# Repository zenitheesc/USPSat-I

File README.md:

<h1 align="center" style="color:white; background-color:black">USP Sat-I</h1>
<h4 align="center">This is an Open Hardware and Software cubesat developed by Zenith EESC-USP for the Cubedesign 2019.</h4>

<p align="center">

</p>

This project was based on a distributed processing architecture and it uses microcontrollers with ARM architecture. The Embedded System is composed by six subsystems:

<a href="https://github.com/zenitheesc/USPSat-AE1/tree/master/M%C3%B3dulo_Ribatski%20v.1.0"><h2>1. Thermal management</h2></a>

This subsystem is primarily responsible for
the active thermal control of the batteries, as proposed by the competition,
in addition to supporting the deployment system of the nanosatellite antennas.

<a href="https://github.com/zenitheesc/USPSat-AE1/tree/master/Varela-Logical_EPS%20v.1.0"><h2>2. Logical EPS</h2></a>

Ensures the monitoring and control of EPS panel parameters,
that is, it performs the measurement of voltage and current levels at various points on the CubeSat;
monitors the temperature of the batteries and acts to keep it always positive, in addition to
carrying out the communication to other subsystems.

<a href="https://github.com/zenitheesc/USPSat-AE1/tree/master/London-Power_EPS%20v.1.1"><h2>3. Power EPS</h2></a>

Functioning as an extension of the previous subsystem, it performs conversions of battery voltage levels to the levels requested within the
hardware, making the necessary distribution, as well as controlling the loading of batteries through solar panels.

<a href="https://github.com/zenitheesc/USPSat-AE1/tree/master/Caurin_CDH%20v.1.0"><h2>4. Comanding and Data Handling</h2></a>

It concentrates one of the processing within CubeSat. It is responsible for managing the information
present in the prototype's internal network, by managing the information received and sent to the Control Base and control of the deployment of the antennas.

<a href="https://github.com/zenitheesc/USPSat-AE1/tree/master/Comin_CTR%20v.1.0"><h2>5. Computer Vision</h2></a>

This subsystem is responsible for image aquisition and on board image processing, for attitude determination using computer vision.

<a href="https://github.com/zenitheesc/USPSat-AE1/tree/master/Alves_ADC%20v.1.0"><h2> 6. Attitude Control </h2></a>

The entire stabilization and pointing system must be done necessary to fulfill the competition missions. For this, the reading is done necessary sensors, activating a reaction wheel, which, by means of the Law of
Conservation of Angular Momentum, manages to act in the attitude of the satellite.

## 7. Structures

Finally, we have the subsystem responsible for the physical integration of all
the subsystems described earlier. All manufacturing issues involving
the physical structure of USPSat is the responsibility of the structures subsystem. The
determination of the materials used, the choice of manufacturing processes and display of all components, aiming at a satisfactory performance in the
vibration, are the main focuses of this subsystem

## Official Documentation

Check out the official documentation [here](https://github.com/zenitheesc/USPSat-AE1/blob/master/USPSat_Report.pdf).

<p align="center">

</p>
<p align = "center">
<a href="zenith.eesc@gmail.com">zenith.eesc@gmail.com</a>
</p>

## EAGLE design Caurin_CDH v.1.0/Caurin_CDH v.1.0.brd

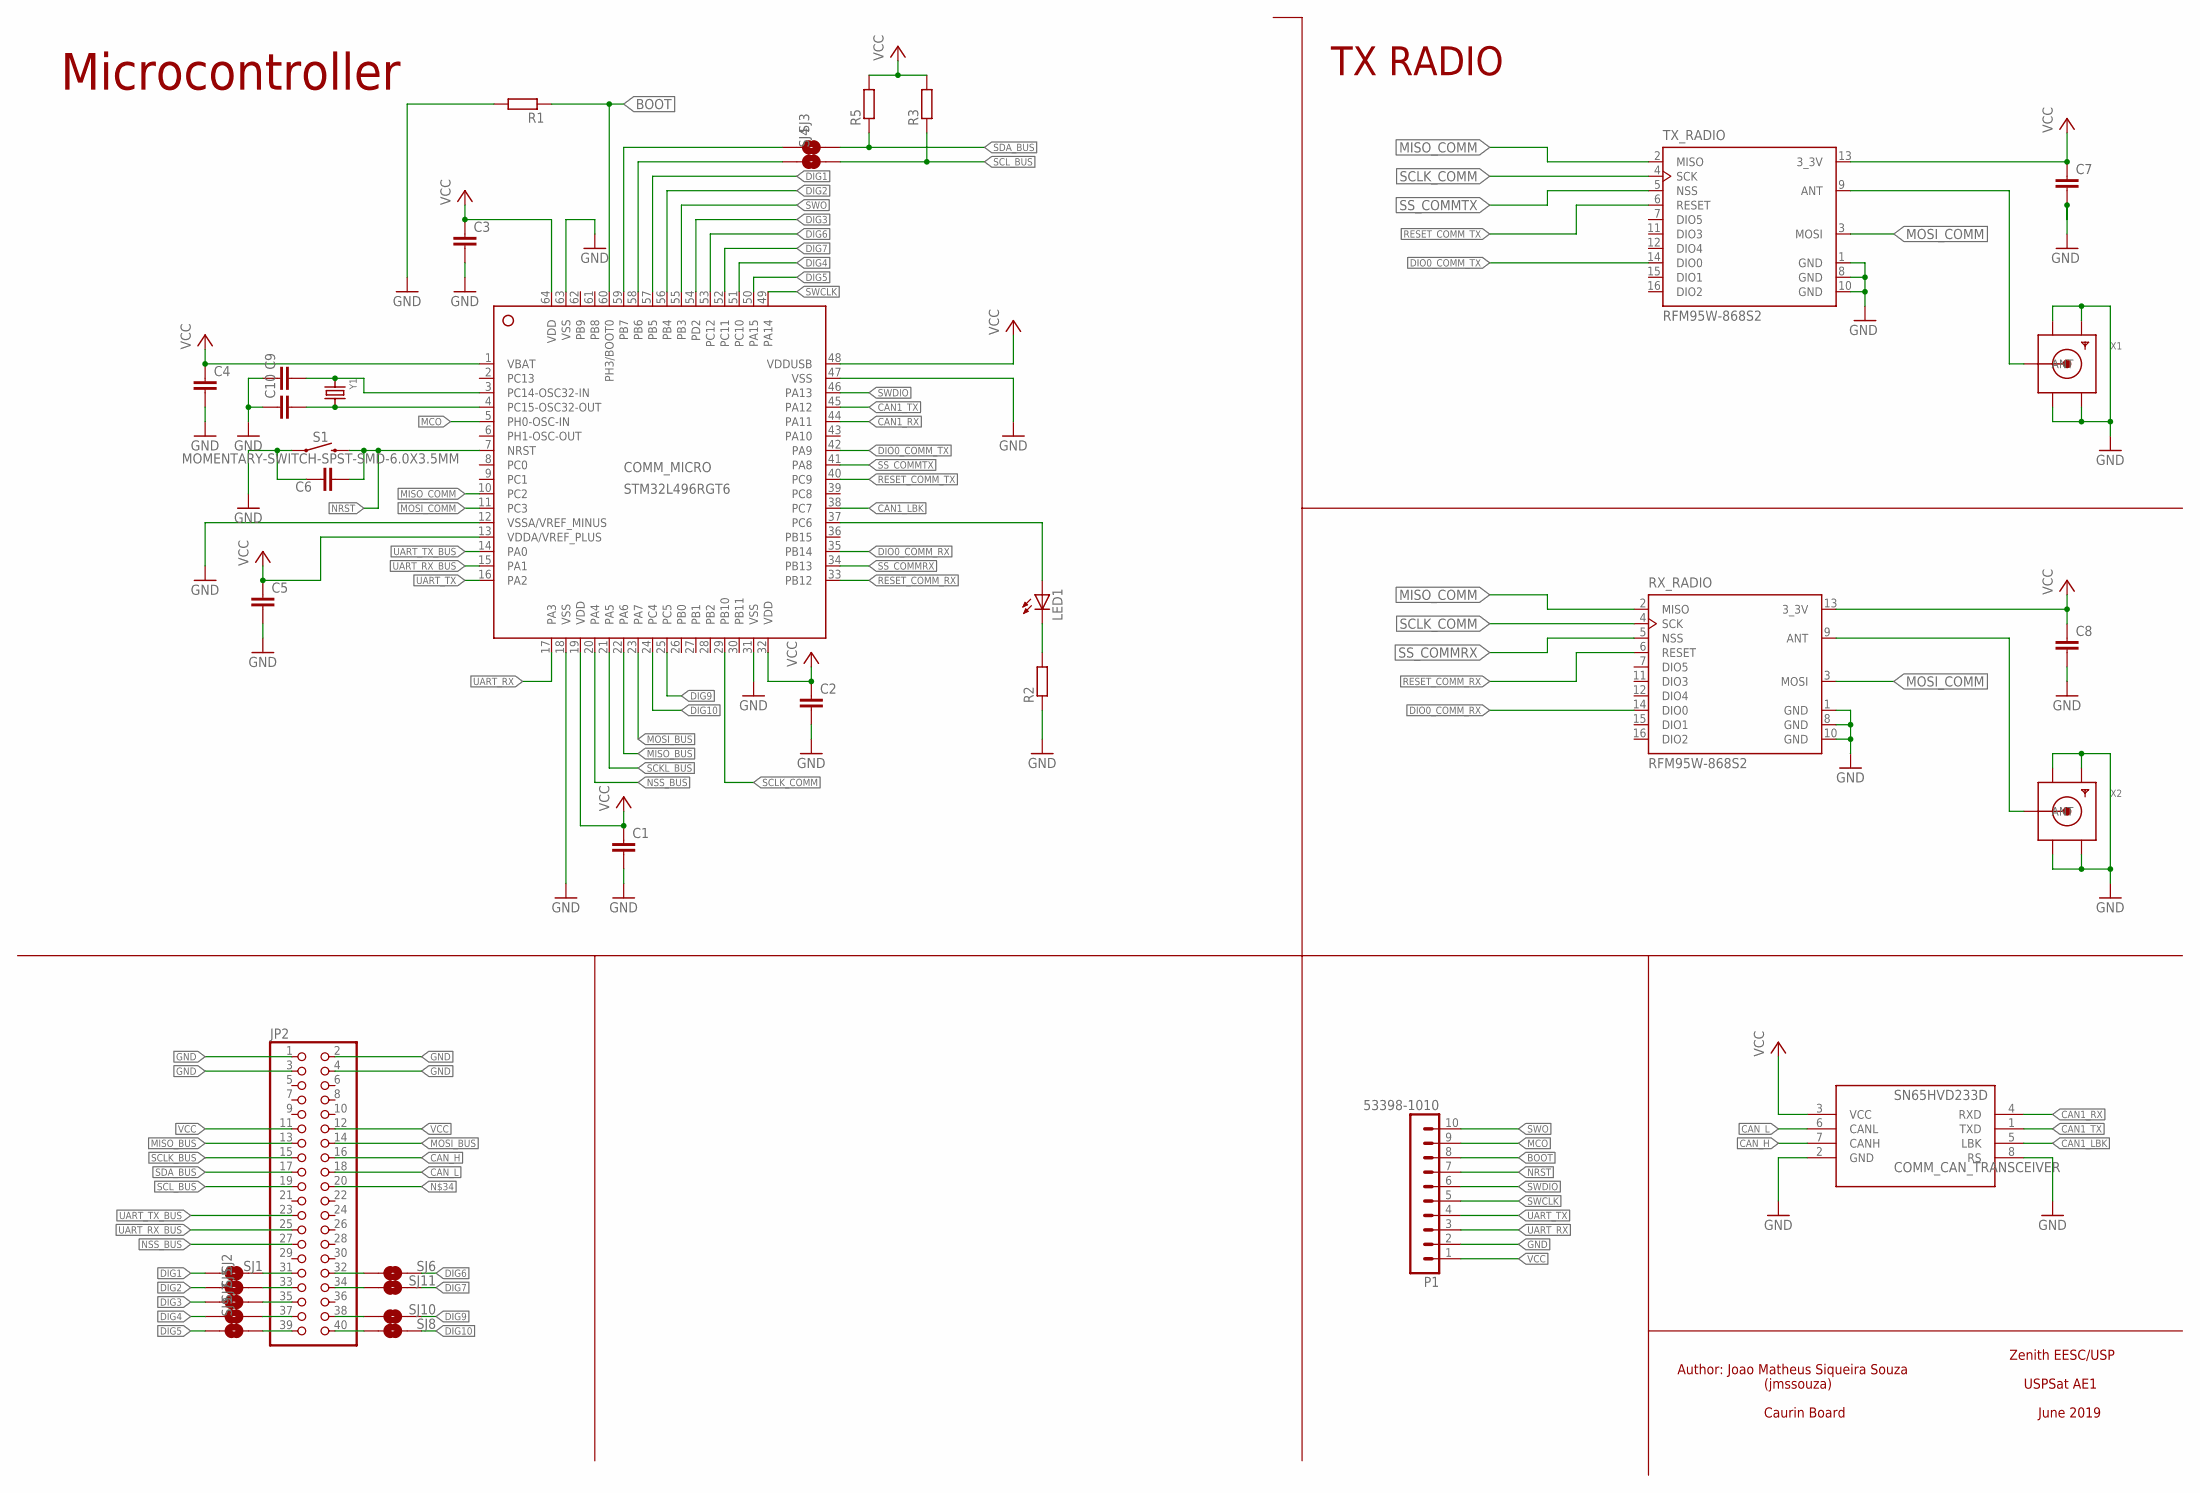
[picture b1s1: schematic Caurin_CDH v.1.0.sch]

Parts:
C1, C2, C3, C4, C5, C6, C7, C8, C9, C10: CC1206; C1206
COMM_CAN_TRANSCEIVER: SN65HVD233D; SOIC8
COMM_MICRO: STM32L496RGT6; LQFP64_10X10
JP2: PINHD-2X20; 2X20
LED1: LED_E; LED_1206
P1: 53398-1010
R1, R2, R3, R5: RR1206; R1206
RX_RADIO: RFM95W-868S2; XCVR_RFM95W-868S2
S1: MOMENTARY-SWITCH-SPST-SMD-6.0X3.5MM; TACTILE_SWITCH_SMD_6.0X3.5MM
SJ1, SJ2, SJ3, SJ4, SJ5, SJ6, SJ7, SJ8, SJ9, SJ10, SJ11: SMD-JUMPER-2
TX_RADIO: RFM95W-868S2; XCVR_RFM95W-868S2
X1, X2: SMACONNECTOR; SMA90_DIP
Y1: CRYSTAL8X3.8SMT; CRYSTAL_8X3.8

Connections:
BOOT: COMM_MICRO.60 (PH3/BOOT0), P1.8, R1.1
CAN1_LBK: COMM_CAN_TRANSCEIVER.5 (LBK), COMM_MICRO.38 (PC7)
CAN1_RX: COMM_CAN_TRANSCEIVER.4 (RXD), COMM_MICRO.44 (PA11)
CAN1_TX: COMM_CAN_TRANSCEIVER.1 (TXD), COMM_MICRO.45 (PA12)
CAN_H: COMM_CAN_TRANSCEIVER.7 (CANH), JP2.16
CAN_L: COMM_CAN_TRANSCEIVER.6 (CANL), JP2.18
DIG1: COMM_MICRO.57 (PB5), SJ1.1
DIG2: COMM_MICRO.56 (PB4), SJ2.1
DIG3: COMM_MICRO.54 (PD2), SJ5.1
DIG4: COMM_MICRO.51 (PC10), SJ7.1
DIG5: COMM_MICRO.50 (PA15), SJ9.1
DIG6: COMM_MICRO.53 (PC12), SJ6.2
DIG7: COMM_MICRO.52 (PC11), SJ11.2
DIG9: COMM_MICRO.25 (PC5), SJ10.2
DIG10: COMM_MICRO.24 (PC4), SJ8.2
DIO0_COMM_RX: COMM_MICRO.35 (PB14), RX_RADIO.14 (DIO0)
DIO0_COMM_TX: COMM_MICRO.42 (PA9), TX_RADIO.14 (DIO0)
GND: C1.2, C2.2, C3.2, C4.2, C5.2, C6.1, C7.2, C8.2, C9.1, C10.1, COMM_CAN_TRANSCEIVER.2 (GND), COMM_CAN_TRANSCEIVER.8 (RS), COMM_MICRO.12 (VSSA/VREF_MINUS), COMM_MICRO.18 (VSS), COMM_MICRO.31 (VSS), COMM_MICRO.47 (VSS), COMM_MICRO.63 (VSS), JP2.1, JP2.2, JP2.3, JP2.4, P1.2, R1.2, R2.1, RX_RADIO.1 (GND), RX_RADIO.8 (GND), RX_RADIO.10 (GND), S1.1, TX_RADIO.1 (GND), TX_RADIO.8 (GND), TX_RADIO.10 (GND), X1.GND1, X1.GND2, X1.GND3, X1.GND4, X2.GND1, X2.GND2, X2.GND3, X2.GND4
MCO: COMM_MICRO.5 (PH0-OSC-IN), P1.9
MISO_BUS: COMM_MICRO.22 (PA6), JP2.13
MISO_COMM: COMM_MICRO.10 (PC2), RX_RADIO.2 (MISO), TX_RADIO.2 (MISO)
MOSI_BUS: COMM_MICRO.23 (PA7), JP2.14
MOSI_COMM: COMM_MICRO.11 (PC3), RX_RADIO.3 (MOSI), TX_RADIO.3 (MOSI)
unnamed: RX_RADIO.9 (ANT), X2.ANTENNA (ANT)
unnamed: COMM_MICRO.37 (PC6), LED1.A
unnamed: LED1.C, R2.2
unnamed: C9.2, COMM_MICRO.3 (PC14-OSC32-IN), Y1.P$1 (1)
unnamed: C10.2, COMM_MICRO.4 (PC15-OSC32-OUT), Y1.P$4 (2)
unnamed: TX_RADIO.9 (ANT), X1.ANTENNA (ANT)
unnamed: JP2.32, SJ6.1
unnamed: COMM_MICRO.59 (PB7), SJ3.1
unnamed: COMM_MICRO.58 (PB6), SJ4.1
unnamed: JP2.34, SJ11.1
unnamed: JP2.38, SJ10.1
unnamed: JP2.40, SJ8.1
unnamed: JP2.37, SJ7.2
unnamed: JP2.39, SJ9.2
unnamed: JP2.35, SJ5.2
unnamed: JP2.33, SJ2.2
unnamed: JP2.31, SJ1.2
NRST: C6.2, COMM_MICRO.7 (NRST), P1.7, S1.2
NSS_BUS: COMM_MICRO.20 (PA4), JP2.27
RESET_COMM_RX: COMM_MICRO.33 (PB12), RX_RADIO.6 (RESET)
RESET_COMM_TX: COMM_MICRO.40 (PC9), TX_RADIO.6 (RESET)
SCKL_BUS: COMM_MICRO.21 (PA5)
SCLK_BUS: JP2.15
SCLK_COMM: COMM_MICRO.29 (PB10), RX_RADIO.4 (SCK), TX_RADIO.4 (SCK)
SCL_BUS: JP2.19, R3.1, SJ4.2
SDA_BUS: JP2.17, R5.1, SJ3.2
SS_COMMRX: COMM_MICRO.34 (PB13), RX_RADIO.5 (NSS)
SS_COMMTX: COMM_MICRO.41 (PA8), TX_RADIO.5 (NSS)
SWCLK: COMM_MICRO.49 (PA14), P1.5
SWDIO: COMM_MICRO.46 (PA13), P1.6
SWO: COMM_MICRO.55 (PB3), P1.10
UART_RX: COMM_MICRO.17 (PA3), P1.3
UART_RX_BUS: COMM_MICRO.15 (PA1), JP2.25
UART_TX: COMM_MICRO.16 (PA2), P1.4
UART_TX_BUS: COMM_MICRO.14 (PA0), JP2.23
VCC: C1.1, C2.1, C3.1, C4.1, C5.1, C7.1, C8.1, COMM_CAN_TRANSCEIVER.3 (VCC), COMM_MICRO.1 (VBAT), COMM_MICRO.13 (VDDA/VREF_PLUS), COMM_MICRO.19 (VDD), COMM_MICRO.32 (VDD), COMM_MICRO.48 (VDDUSB), COMM_MICRO.64 (VDD), JP2.11, JP2.12, P1.1, R3.2, R5.2, RX_RADIO.13 (3_3V), TX_RADIO.13 (3_3V)

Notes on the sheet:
TX RADIO
Author: Joao Matheus Siqueira Souza
Zenith EESC/USP
USPSat AE1
(jmssouza)
June 2019
Caurin Board
Microcontroller

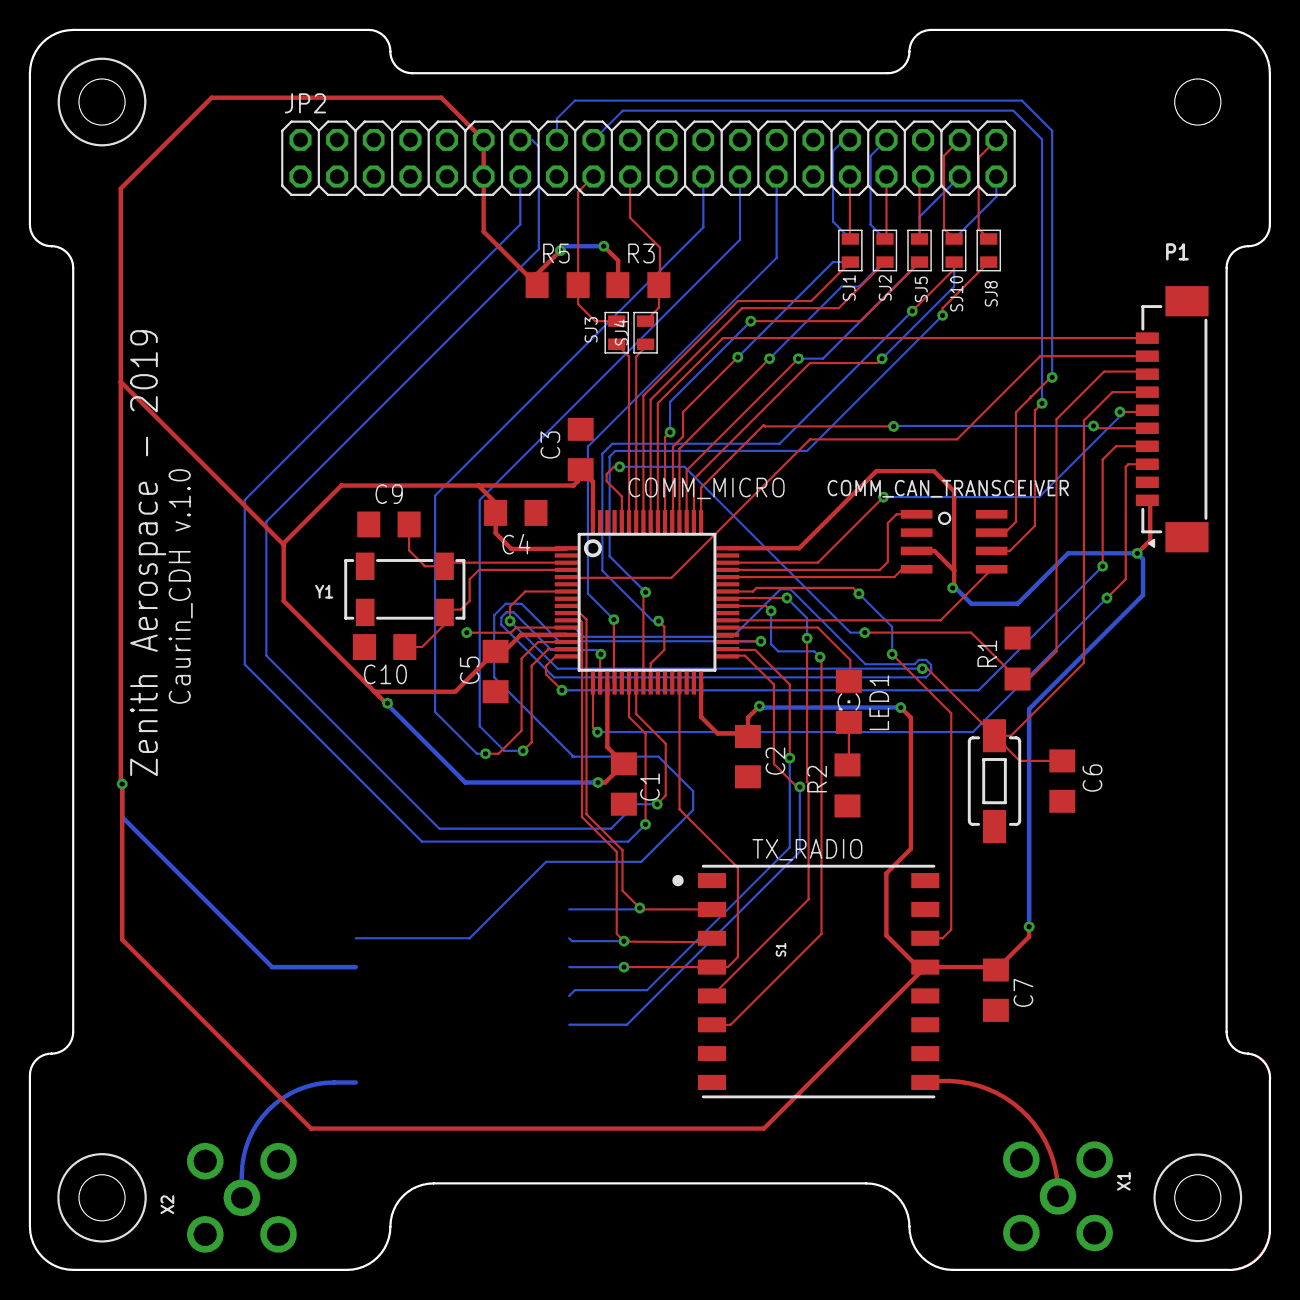
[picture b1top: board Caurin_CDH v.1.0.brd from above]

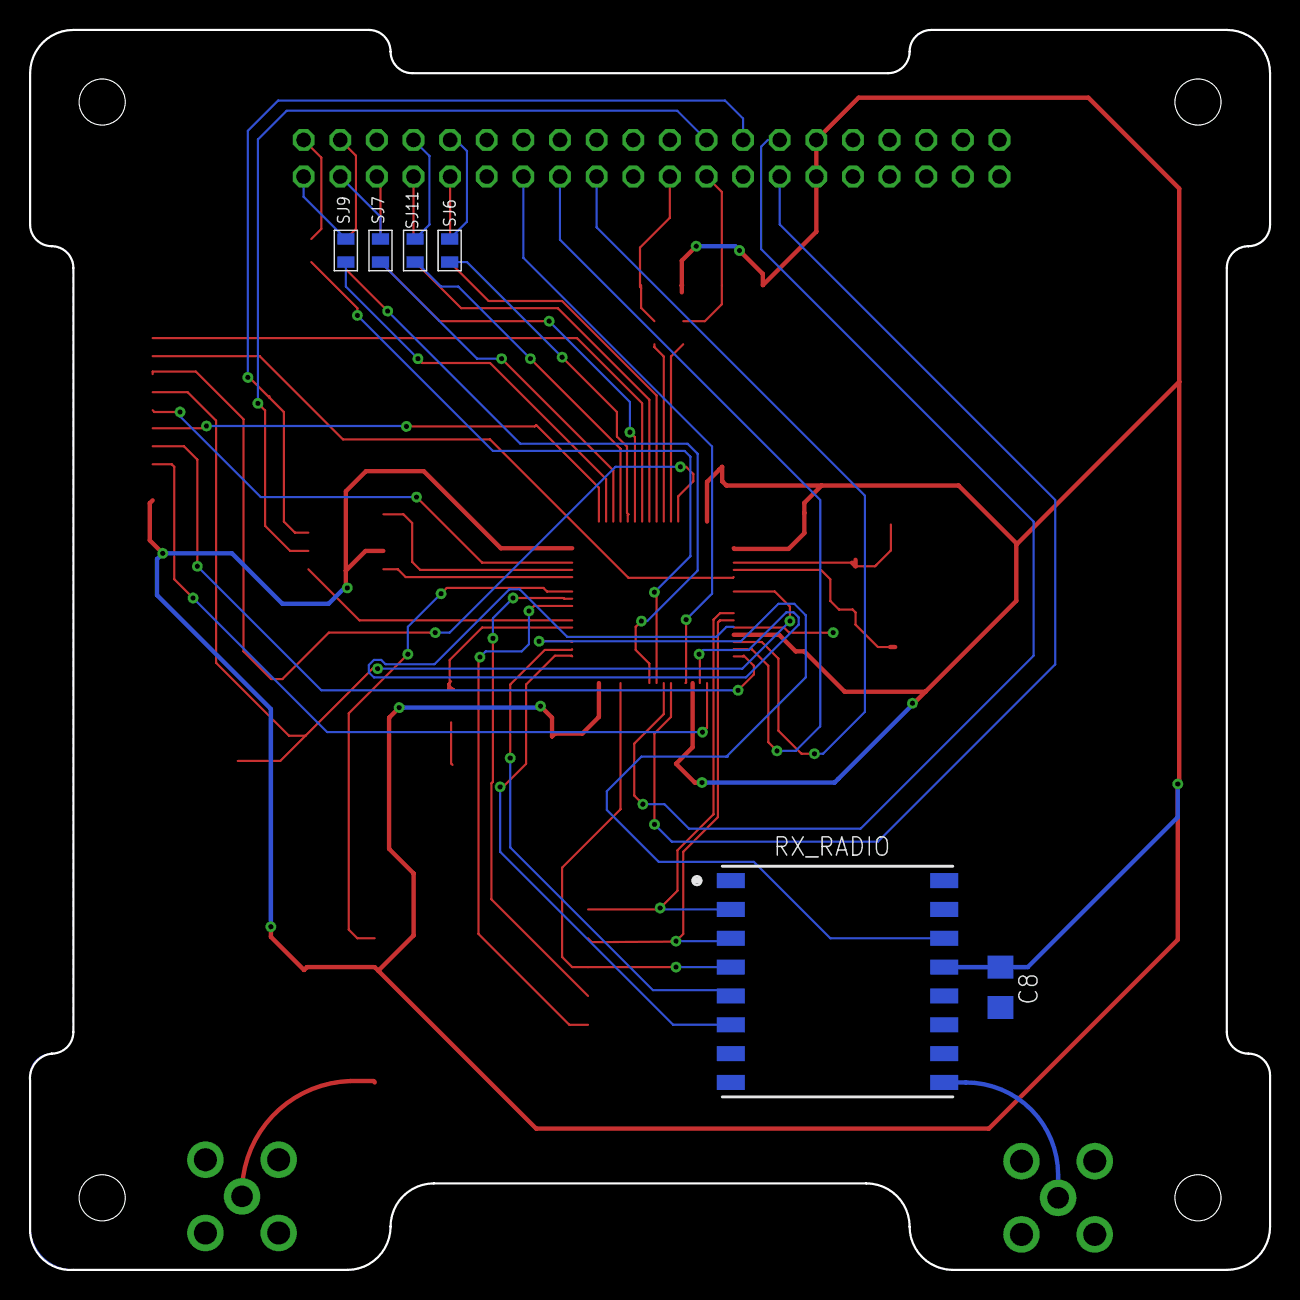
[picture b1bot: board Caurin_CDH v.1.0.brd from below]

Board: 2 copper layers, 86.0 x 86.0 mm, 36 parts (6 on the bottom side), 57 nets.

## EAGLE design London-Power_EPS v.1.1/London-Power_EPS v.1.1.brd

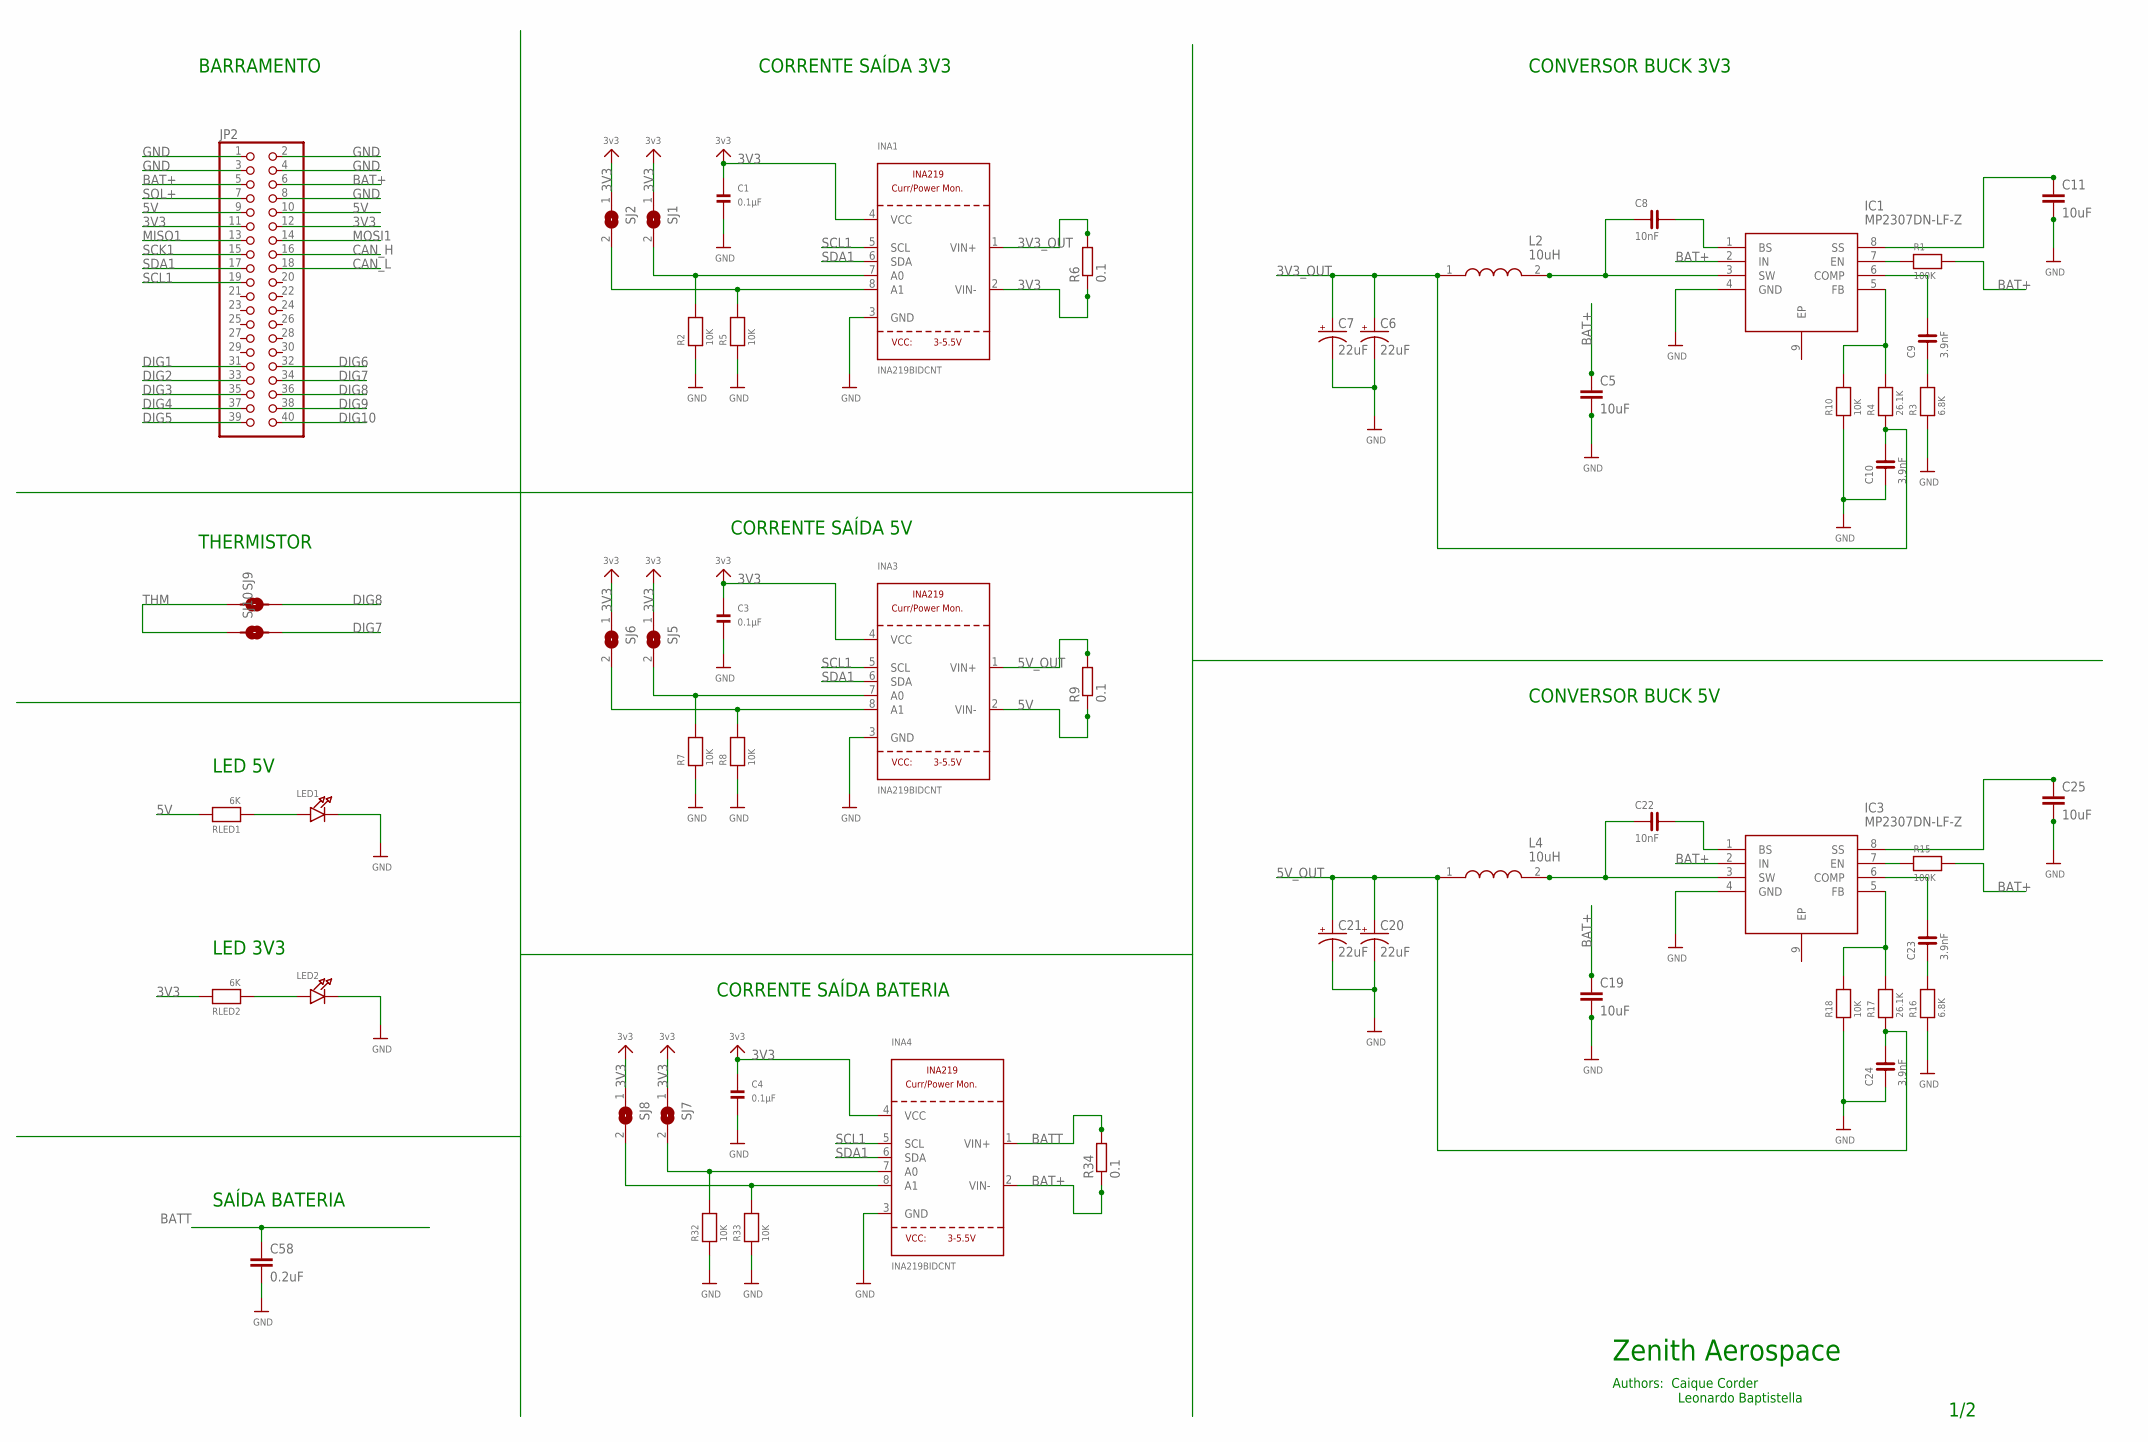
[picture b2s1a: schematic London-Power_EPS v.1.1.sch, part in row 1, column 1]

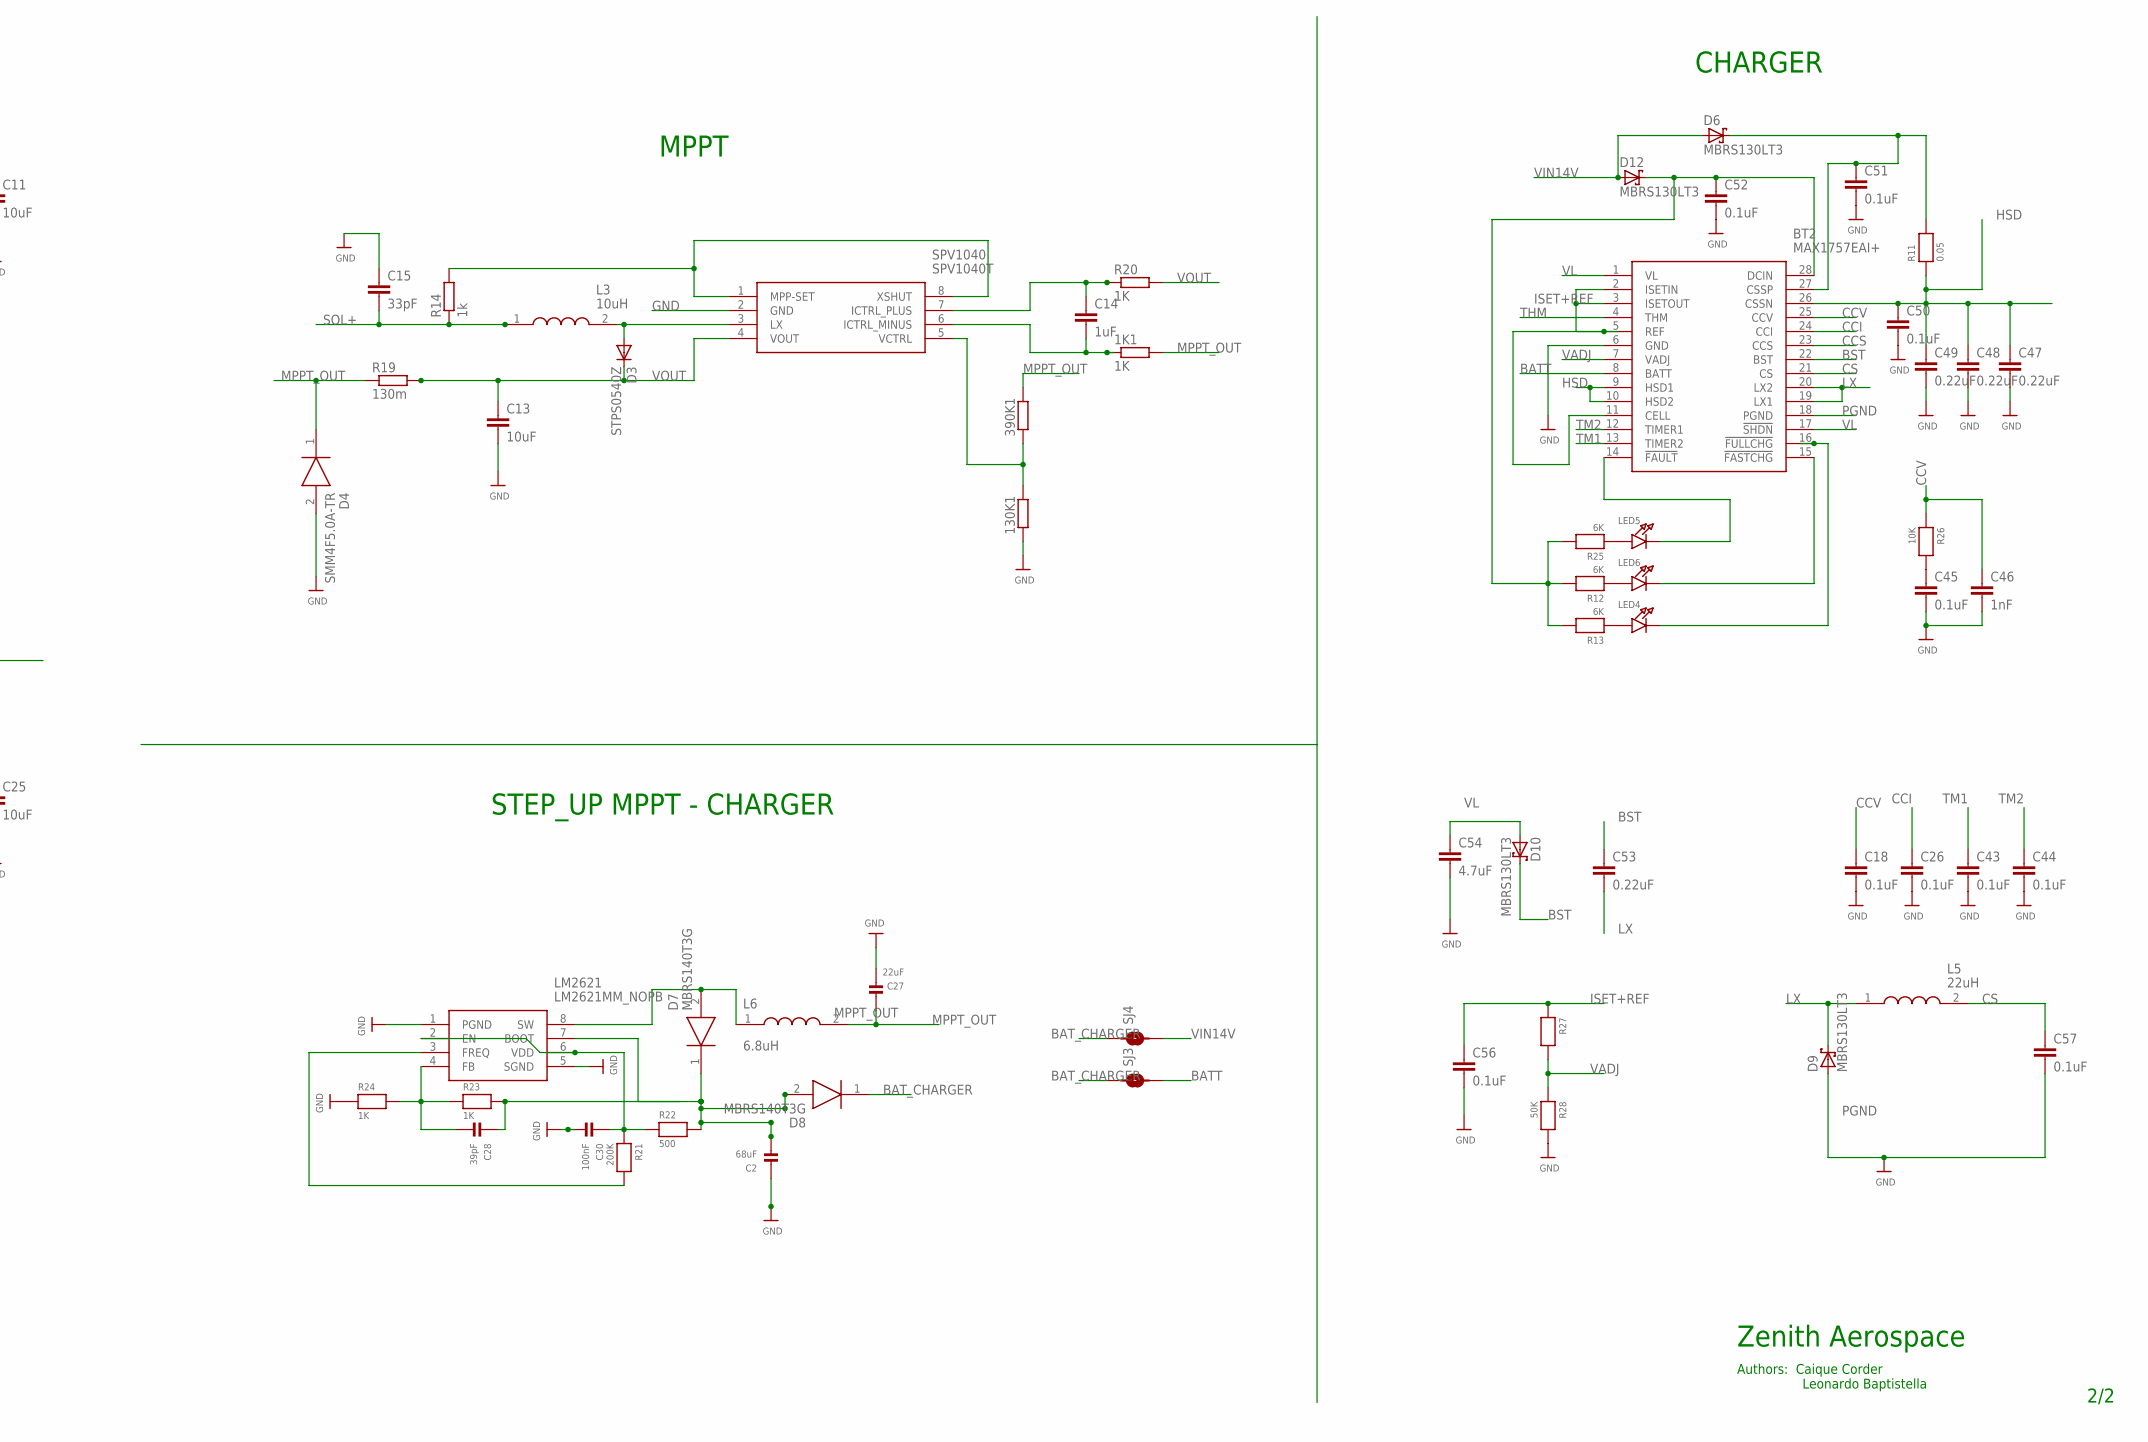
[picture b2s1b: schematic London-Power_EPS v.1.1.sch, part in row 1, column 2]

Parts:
1K1: 1K; R1206
130K1, 390K1: RR1206; R1206
BT2: MAX1757EAI+; SOP65P778X199-28N
C1, C3, C4: 0.1µF; 1206
C2: 68uF; 1206
C5, C11, C13, C19, C25: 10uF; C1206
C6, C7, C20, C21: 22uF; EIA3528
C8, C22: 10nF; 0805
C9, C10, C23, C24: 3.9nF; 0805
C14: 1uF; C1206
C15: 33pF; C1206
C18, C26, C43, C44, C45, C50, C51, C52, C56, C57: 0.1uF; C1206
C27: 22uF; 1206
C28: 39pF; 1206
C30: 100nF; 1206
C46: 1nF; C1206
C47, C48, C49, C53: 0.22uF; C1206
C54: 4.7uF; C1206
C58: 0.2uF; C1206
D3: STPS0540Z; SOD-123_MINI-SMA
D4: SMM4F5.0A-TR; STMITE
D6, D9, D10, D12: MBRS130LT3; SMB
D7, D8: MBRS140T3G; DIOM5436X247N
IC1, IC3: MP2307DN-LF-Z; SOIC127P600X170-9N
INA1, INA3, INA4: INA219BIDCNT; SOT23-8
JP2: PINHD-2X20; 2X20
L2, L3, L4: 10uH; SRR1280-220M
L5: 22uH; INDPM4848X280N
L6: 6.8uH; SRR1280-220M
LED1, LED2, LED4, LED5, LED6: LED1206; CHIPLED_1206
LM2621: LM2621MM_NOPB; SOP65P490X110-8N
R1, R15: 100K; 1206
R2, R5, R7, R8, R10, R18, R26, R32, R33: 10K; 1206
R3, R16: 6.8K; 1206
R4, R17: 26.1K; 1206
R6, R9, R34: 0.1; R2512
R11: 0.05; 1206
R12, R13, R25: 6K; 1206
R14: 1k; R1206
R19: 130m; R1206
R20: 1K; R1206
R21: 200K; 1206
R22: 500; 1206
R23, R24: 1K; 1206
R27: RESISTOR1206; 1206
R28: 50K; 1206
RLED1, RLED2: 6K; 1206
SJ1, SJ2, SJ5, SJ6, SJ7, SJ8: SOLDERJUMPERREFLOW_NOPASTE; SOLDERJUMPER_REFLOW_NOPASTE
SJ3, SJ4, SJ9, SJ10: SMD-JUMPER-2
SPV1040: SPV1040T; SOP65P640X120-8N

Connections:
3V3: C1.1, C3.1, C4.1, INA1.2 (VIN-), INA1.4 (VCC), INA3.4 (VCC), INA4.4 (VCC), JP2.11, JP2.12, R6.1, RLED2.2, SJ1.1, SJ2.1, SJ5.1, SJ6.1, SJ7.1, SJ8.1
3V3_OUT: C6.A (+), C7.A (+), C10.2, INA1.1 (VIN+), L2.1, R4.1, R6.2
5V: INA3.2 (VIN-), JP2.9, JP2.10, R9.1, RLED1.2
5V_OUT: C20.A (+), C21.A (+), C24.2, INA3.1 (VIN+), L4.1, R9.2, R17.1
BAT+: C5.1, C19.1, IC1.2 (IN), IC3.2 (IN), INA4.2 (VIN-), JP2.5, JP2.6, R1.2, R15.2, R34.1
BATT: BT2.8 (BATT), C58.1, INA4.1 (VIN+), R34.2, SJ3.2
BAT_CHARGER: D8.1 (K), SJ3.1, SJ4.1
BST: BT2.22 (BST), C53.1, D10.C
CAN_H: JP2.16
CAN_L: JP2.18
CCI: BT2.24 (CCI), C26.1
CCS: BT2.23 (CCS)
CCV: BT2.25 (CCV), C18.1, C46.1, R26.1
CS: BT2.21 (CS), C57.1, L5.2
DIG1: JP2.31
DIG2: JP2.33
DIG3: JP2.35
DIG4: JP2.37
DIG5: JP2.39
DIG6: JP2.32
DIG7: JP2.34, SJ10.2
DIG8: JP2.36, SJ9.2
DIG9: JP2.38
DIG10: JP2.40
GND: 130K1.1, BT2.6 (GND), C1.2, C2.1, C3.2, C4.2, C5.2, C6.C (-), C7.C (-), C10.1, C11.2, C13.2, C15.1, C18.2, C19.2, C20.C (-), C21.C (-), C24.1, C25.2, C26.2, C27.2, C30.2, C43.2, C44.2, C45.2, C46.2, C47.2, C48.2, C49.2, C50.2, C51.2, C52.2, C54.2, C56.2, C58.2, D4.2 (A), IC1.4 (GND), IC3.4 (GND), INA1.3 (GND), INA3.3 (GND), INA4.3 (GND), JP2.1, JP2.2, JP2.3, JP2.4, JP2.8, LED1.C, LED2.C, LM2621.1 (PGND), LM2621.5 (SGND), R2.1, R3.1, R5.1, R7.1, R8.1, R10.1, R16.1, R18.1, R24.1, R28.2, R32.1, R33.1, SPV1040.2 (GND)
HSD: BT2.9 (HSD1), BT2.10 (HSD2), BT2.26 (CSSN), C47.1, C48.1, C49.1, C50.1, R11.1
ISET+REF: BT2.2 (ISETIN), BT2.3 (ISETOUT), BT2.5 (REF), BT2.11 (CELL), C56.1, R27.1
LX: BT2.19 (LX1), BT2.20 (LX2), C53.2, D9.C, L5.1
MISO1: JP2.13
MOSI1: JP2.14
MPPT_OUT: 1K1.2, 390K1.2, C27.1, D4.1 (K), L6.2, R19.1
unnamed: INA1.8 (A1), R5.2, SJ2.2
unnamed: INA1.7 (A0), R2.2, SJ1.2
unnamed: C8.2, IC1.1 (BS)
unnamed: C11.1, IC1.8 (SS)
unnamed: INA3.8 (A1), R8.2, SJ6.2
unnamed: INA3.7 (A0), R7.2, SJ5.2
unnamed: C8.1, IC1.3 (SW), L2.2
unnamed: IC1.7 (EN), R1.1
unnamed: C9.2, IC1.6 (COMP)
unnamed: C9.1, R3.2
unnamed: IC1.5 (FB), R4.2, R10.2
unnamed: LED2.A, RLED2.1
unnamed: LED1.A, RLED1.1
unnamed: LED6.A, R12.1
unnamed: BT2.28 (DCIN), C52.1, D12.C, R12.2, R13.2, R25.2
unnamed: BT2.14 (!FAULT), LED5.C
unnamed: D3.A, L3.2, SPV1040.3 (LX)
unnamed: R14.2, SPV1040.1 (MPP-SET), SPV1040.8 (XSHUT)
unnamed: C22.2, IC3.1 (BS)
unnamed: C25.1, IC3.8 (SS)
unnamed: C22.1, IC3.3 (SW), L4.2
unnamed: IC3.7 (EN), R15.1
unnamed: C23.2, IC3.6 (COMP)
unnamed: C23.1, R16.2
unnamed: IC3.5 (FB), R17.2, R18.2
unnamed: C14.1, R20.1, SPV1040.7 (ICTRL_PLUS)
unnamed: 1K1.1, C14.2, SPV1040.6 (ICTRL_MINUS)
unnamed: 130K1.2, 390K1.1, SPV1040.5 (VCTRL)
unnamed: BT2.15 (!FASTCHG), LED6.C
unnamed: BT2.16 (!FULLCHG), LED4.C
unnamed: INA4.8 (A1), R33.2, SJ8.2
unnamed: C2.2, D7.1 (K), D8.2 (A), LM2621.7 (BOOT), R22.2
unnamed: C30.1, LM2621.2 (EN), LM2621.6 (VDD), R21.1, R22.1
unnamed: LM2621.3 (FREQ), R21.2
unnamed: C28.2, LM2621.4 (FB), R23.1, R24.2
unnamed: C28.1, R23.2
unnamed: LED4.A, R13.1
unnamed: D7.2 (A), L6.1, LM2621.8 (SW)
unnamed: INA4.7 (A0), R32.2, SJ7.2
unnamed: LED5.A, R25.1
unnamed: C45.1, R26.2
unnamed: BT2.27 (CSSP), C51.1, D6.C, R11.2
PGND: BT2.18 (PGND), C57.2, D9.A
SCK1: JP2.15
SCL1: INA1.5 (SCL), INA3.5 (SCL), INA4.5 (SCL), JP2.19
SDA1: INA1.6 (SDA), INA3.6 (SDA), INA4.6 (SDA), JP2.17
SOL+: C15.2, JP2.7, L3.1, R14.1
THM: BT2.4 (THM), SJ9.1, SJ10.1
TM1: BT2.13 (TIMER2), C43.1
TM2: BT2.12 (TIMER1), C44.1
VADJ: BT2.7 (VADJ), R27.2, R28.1
VIN14V: D6.A, D12.A, SJ4.2
VL: BT2.1 (VL), BT2.17 (!SHDN), C54.1, D10.A
VOUT: C13.1, D3.C, R19.2, R20.2, SPV1040.4 (VOUT)

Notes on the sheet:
CORRENTE SAÍDA 3V3
CORRENTE SAÍDA 5V
CORRENTE SAÍDA BATERIA
CONVERSOR BUCK 3V3
CONVERSOR BUCK 5V
MPPT
STEP_UP MPPT - CHARGER
CHARGER
BARRAMENTO
THERMISTOR
LED 5V
LED 3V3
SAÍDA BATERIA
Zenith Aerospace
Authors: Caique Corder Leonardo Baptistella
1/2
2/2

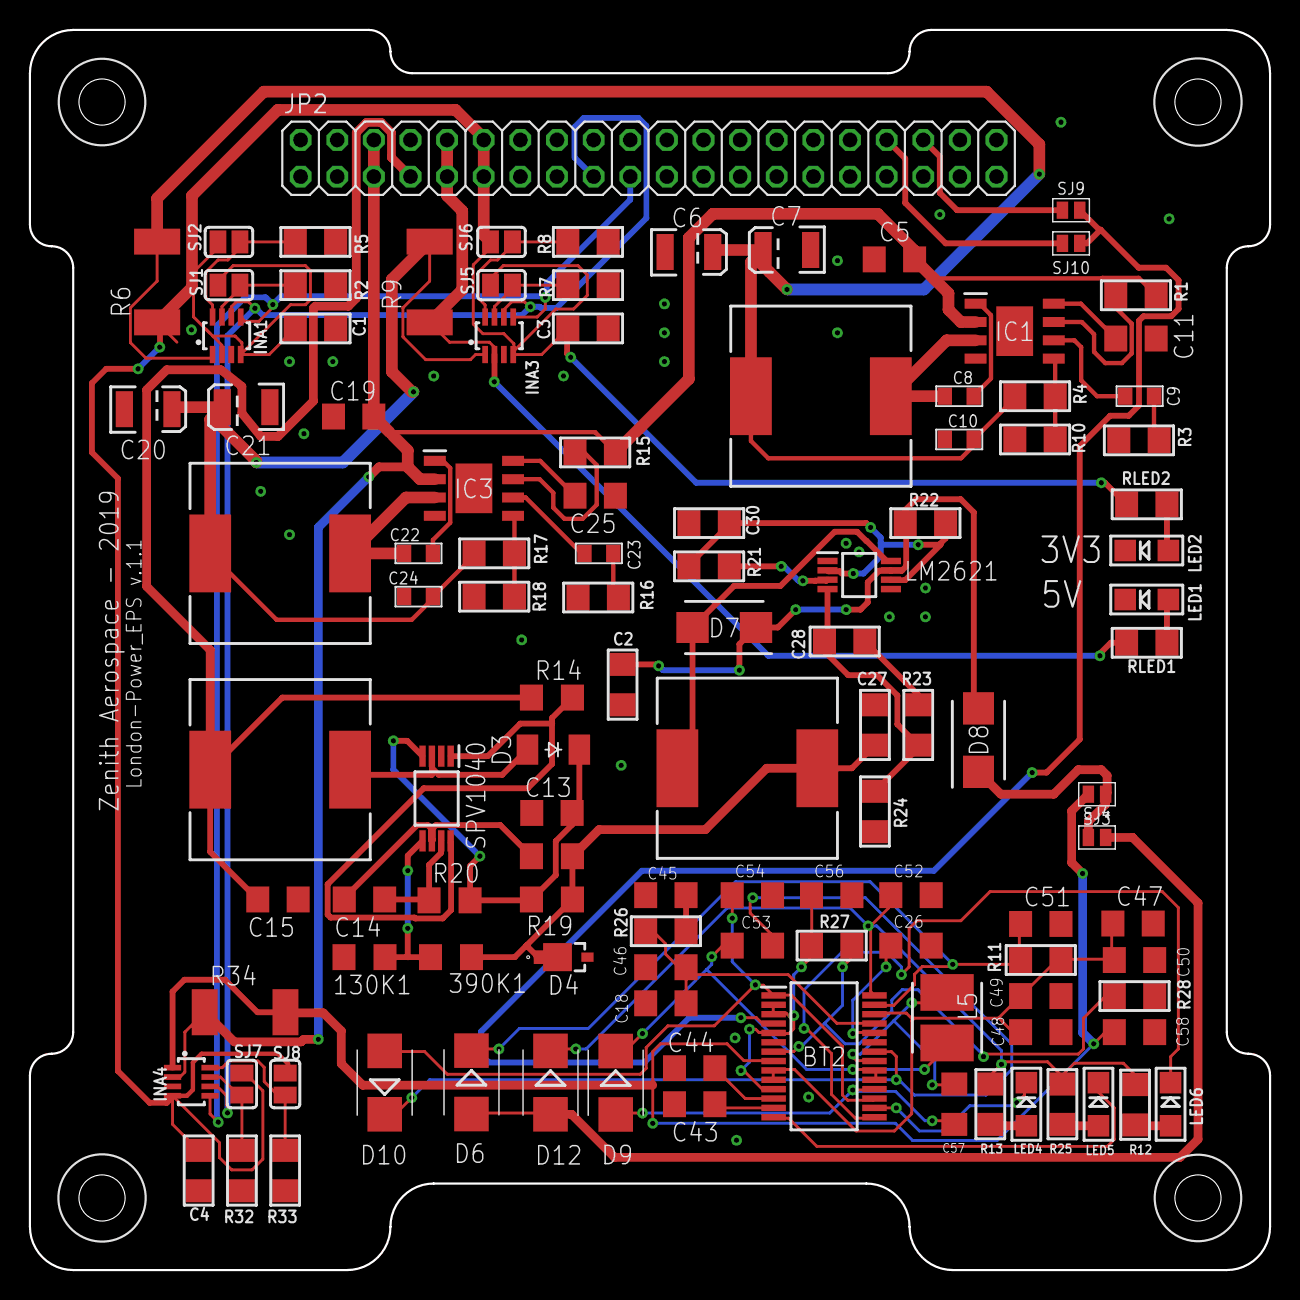
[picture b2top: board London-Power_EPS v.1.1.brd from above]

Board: 2 copper layers, 86.0 x 86.0 mm, 114 parts (0 on the bottom side), 71 nets.

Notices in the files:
parts and their libraries:
SparkFun-Electromechanical: Licensing: Creative Commons ShareAlike 4.0 International - https://creativecommons.org/licenses/by-sa/4.0
microbuilder: This work is placed in the public domain, and may be freely used for commercial and non-commercial work with the following conditions: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
